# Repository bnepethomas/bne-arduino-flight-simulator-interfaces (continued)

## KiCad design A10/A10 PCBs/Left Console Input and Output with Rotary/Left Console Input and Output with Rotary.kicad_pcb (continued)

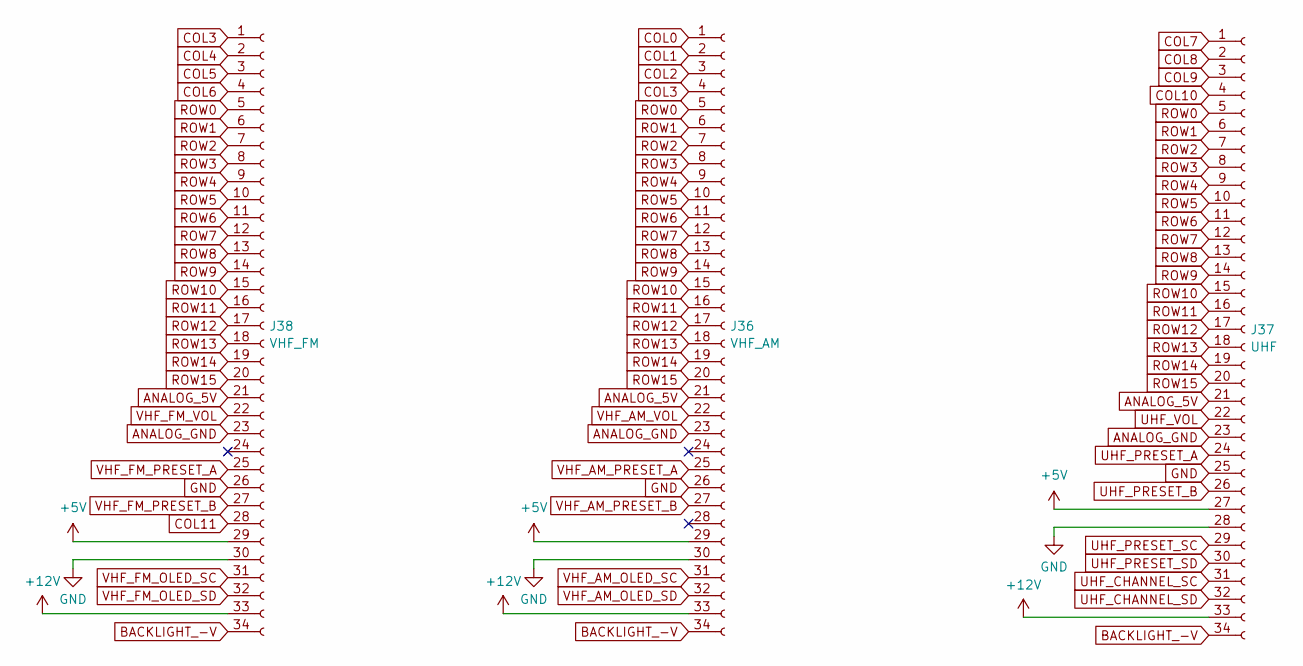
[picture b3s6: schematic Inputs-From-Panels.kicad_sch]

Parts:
J36: VHF_AM; IDC-Header_2x17_P2.54mm_Vertical
J37: UHF; IDC-Header_2x17_P2.54mm_Vertical
J38: VHF_FM; IDC-Header_2x17_P2.54mm_Vertical

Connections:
+12V: J36.33, J37.33, J38.33; also elsewhere on the board
BACKLIGHT_-V: J36.34, J37.34, J38.34; also elsewhere on the board
COL0: J36.1; also elsewhere on the board
COL1: J36.2; also elsewhere on the board
COL2: J36.3; also elsewhere on the board
COL3: J36.4, J38.1; also elsewhere on the board
COL4: J38.2; also elsewhere on the board
COL5: J38.3; also elsewhere on the board
COL6: J38.4; also elsewhere on the board
COL7: J37.1; also elsewhere on the board
COL8: J37.2; also elsewhere on the board
COL9: J37.3; also elsewhere on the board
COL10: J37.4; also elsewhere on the board
COL11: J38.28; also elsewhere on the board
ROW0: J36.5, J37.5, J38.5; also elsewhere on the board
ROW1: J36.6, J37.6, J38.6; also elsewhere on the board
ROW2: J36.7, J37.7, J38.7; also elsewhere on the board
ROW3: J36.8, J37.8, J38.8; also elsewhere on the board
ROW4: J36.9, J37.9, J38.9; also elsewhere on the board
ROW5: J36.10, J37.10, J38.10; also elsewhere on the board
ROW6: J36.11, J37.11, J38.11; also elsewhere on the board
ROW7: J36.12, J37.12, J38.12; also elsewhere on the board
ROW8: J36.13, J37.13, J38.13; also elsewhere on the board
ROW9: J36.14, J37.14, J38.14; also elsewhere on the board
ROW10: J36.15, J37.15, J38.15; also elsewhere on the board
ROW11: J36.16, J37.16, J38.16; also elsewhere on the board
ROW12: J36.17, J37.17, J38.17; also elsewhere on the board
ROW13: J36.18, J37.18, J38.18; also elsewhere on the board
ROW14: J36.19, J37.19, J38.19; also elsewhere on the board
ROW15: J36.20, J37.20, J38.20; also elsewhere on the board
UHF_CHANNEL_SC: J37.31; also elsewhere on the board
UHF_CHANNEL_SD: J37.32; also elsewhere on the board
UHF_PRESET_A: J37.24; also elsewhere on the board
UHF_PRESET_B: J37.26; also elsewhere on the board
UHF_PRESET_SC: J37.29; also elsewhere on the board
UHF_PRESET_SD: J37.30; also elsewhere on the board
UHF_VOL: J37.22; also elsewhere on the board
VHF_AM_OLED_SC: J36.31; also elsewhere on the board
VHF_AM_OLED_SD: J36.32; also elsewhere on the board
VHF_AM_PRESET_A: J36.25; also elsewhere on the board
VHF_AM_PRESET_B: J36.27; also elsewhere on the board
VHF_AM_VOL: J36.22; also elsewhere on the board
VHF_FM_OLED_SC: J38.31; also elsewhere on the board
VHF_FM_OLED_SD: J38.32; also elsewhere on the board
VHF_FM_PRESET_A: J38.25; also elsewhere on the board
VHF_FM_PRESET_B: J38.27; also elsewhere on the board
VHF_FM_VOL: J38.22; also elsewhere on the board

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
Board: 2 copper layers, 87 parts (0 on the bottom side), 144 nets, no tracks yet.

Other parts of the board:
MH1: MountingHole_3.2mm

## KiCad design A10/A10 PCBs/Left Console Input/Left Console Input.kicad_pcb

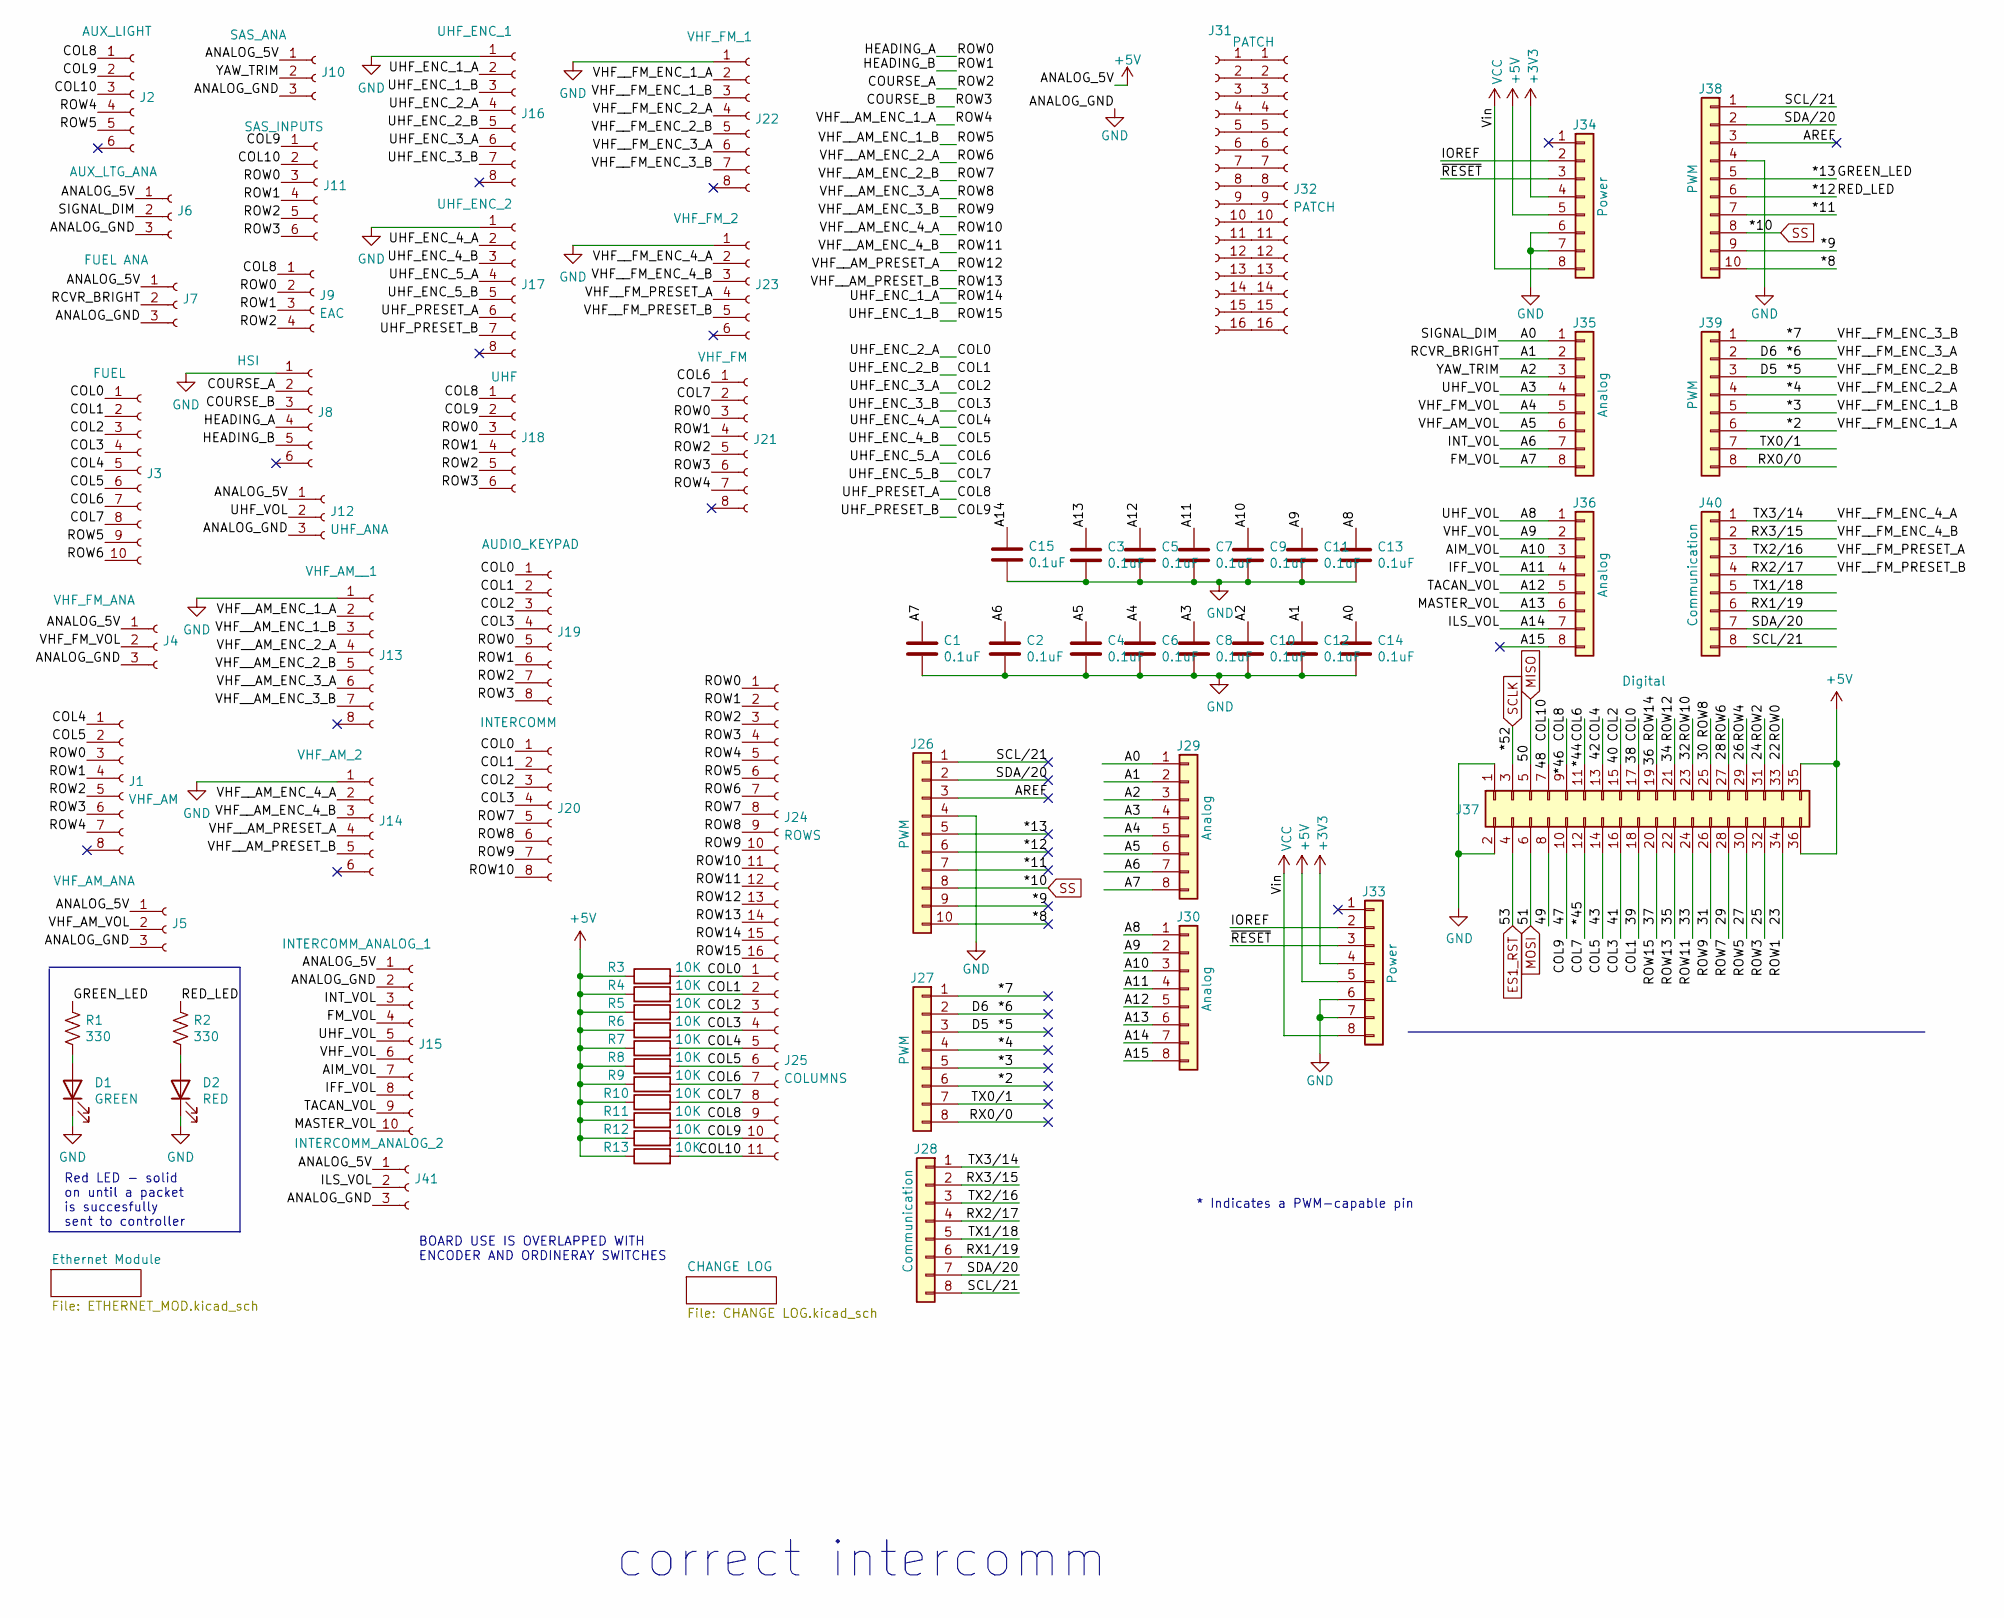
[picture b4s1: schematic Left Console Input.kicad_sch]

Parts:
C1, C2, C3, C4, C5, C6, C7, C8, C9, C10, C11, C12, C13, C14, C15: 0.1uF; C_Disc_D6.0mm_W2.5mm_P5.00mm
D1: GREEN; LED_D3.0mm
D2: RED; LED_D3.0mm
J1: VHF_AM; Molex_KK-254_AE-6410-08A_1x08_P2.54mm_Vertical
J2: AUX_LIGHT; Molex_KK-254_AE-6410-06A_1x06_P2.54mm_Vertical
J3: FUEL; Molex_KK-254_AE-6410-10A_1x10_P2.54mm_Vertical
J4: VHF_FM_ANA; Molex_KK-254_AE-6410-03A_1x03_P2.54mm_Vertical
J5: VHF_AM_ANA; Molex_KK-254_AE-6410-03A_1x03_P2.54mm_Vertical
J6: AUX_LTG_ANA; Molex_KK-254_AE-6410-03A_1x03_P2.54mm_Vertical
J7: FUEL ANA; Molex_KK-254_AE-6410-03A_1x03_P2.54mm_Vertical
J8: HSI; Molex_KK-254_AE-6410-06A_1x06_P2.54mm_Vertical
J9: EAC; Molex_KK-254_AE-6410-04A_1x04_P2.54mm_Vertical
J10: SAS_ANA; Molex_KK-254_AE-6410-03A_1x03_P2.54mm_Vertical
J11: SAS_INPUTS; Molex_KK-254_AE-6410-06A_1x06_P2.54mm_Vertical
J12: UHF_ANA; Molex_KK-254_AE-6410-03A_1x03_P2.54mm_Vertical
J13: VHF_AM__1; Molex_KK-254_AE-6410-08A_1x08_P2.54mm_Vertical
J14: VHF_AM_2; Molex_KK-254_AE-6410-06A_1x06_P2.54mm_Vertical
J15: INTERCOMM_ANALOG_1; Molex_KK-254_AE-6410-10A_1x10_P2.54mm_Vertical
J16: UHF_ENC_1; Molex_KK-254_AE-6410-08A_1x08_P2.54mm_Vertical
J17: UHF_ENC_2; Molex_KK-254_AE-6410-08A_1x08_P2.54mm_Vertical
J18: UHF; Molex_KK-254_AE-6410-06A_1x06_P2.54mm_Vertical
J19: AUDIO_KEYPAD; Molex_KK-254_AE-6410-08A_1x08_P2.54mm_Vertical
J20: INTERCOMM; Molex_KK-254_AE-6410-08A_1x08_P2.54mm_Vertical
J21: VHF_FM; Molex_KK-254_AE-6410-08A_1x08_P2.54mm_Vertical
J22: VHF_FM_1; Molex_KK-254_AE-6410-08A_1x08_P2.54mm_Vertical
J23: VHF_FM_2; Molex_KK-254_AE-6410-06A_1x06_P2.54mm_Vertical
J24: ROWS; PinHeader_1x16_P2.54mm_Vertical
J25: COLUMNS; PinHeader_1x11_P2.54mm_Vertical
J26, J38: PWM; PinSocket_1x10_P2.54mm_Vertical
J27, J39: PWM; PinSocket_1x08_P2.54mm_Vertical
J28, J40: Communication; PinSocket_1x08_P2.54mm_Vertical
J29, J30, J35, J36: Analog; PinSocket_1x08_P2.54mm_Vertical
J31, J32: PATCH; PinHeader_1x16_P2.54mm_Vertical
J33, J34: Power; PinSocket_1x08_P2.54mm_Vertical
J37: Digital; PinSocket_2x18_P2.54mm_Vertical
J41: INTERCOMM_ANALOG_2; Molex_KK-254_AE-6410-03A_1x03_P2.54mm_Vertical
R1, R2: 330; R_Axial_DIN0204_L3.6mm_D1.6mm_P2.54mm_Vertical
R3, R4, R5, R6, R7, R8, R9, R10, R11, R12, R13: 10K; R_Axial_DIN0204_L3.6mm_D1.6mm_P2.54mm_Vertical

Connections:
+3V3: J33.4, J34.4; also elsewhere on the board
+5V: J4.1, J5.1, J6.1, J7.1, J10.1, J12.1, J15.1, J33.5, J34.5, J37.35, J37.36, J41.1, R3.1, R4.1, R5.1, R6.1, R7.1, R8.1, R9.1, R10.1, R11.1, R12.1, R13.1
/22: J1.3, J8.4, J9.2, J11.3, J18.3, J19.5, J21.3, J24.1, J37.33
/23: J1.4, J8.5, J9.3, J11.4, J18.4, J19.6, J21.4, J24.2, J37.34
/24: J1.5, J8.2, J9.4, J11.5, J18.5, J19.7, J21.5, J24.3, J37.31
/25: J1.6, J8.3, J11.6, J18.6, J19.8, J21.6, J24.4, J37.32
/26: J1.7, J2.4, J13.2, J21.7, J24.5, J37.29
/27: J2.5, J3.9, J13.3, J24.6, J37.30
/28: J3.10, J13.4, J24.7, J37.27
/29: J13.5, J20.5, J24.8, J37.28
/30: J13.6, J20.6, J24.9, J37.25
/31: J13.7, J20.7, J24.10, J37.26
/32: J14.2, J20.8, J24.11, J37.23
/33: J14.3, J24.12, J37.24
/34: J14.4, J24.13, J37.21
/35: J14.5, J24.14, J37.22
/36: J16.2, J24.15, J37.19
/37: J16.3, J24.16, J37.20
/38: J3.1, J16.4, J19.1, J20.1, J25.1, J37.17, R3.2
/39: J3.2, J16.5, J19.2, J20.2, J25.2, J37.18, R4.2
/40: J3.3, J16.6, J19.3, J20.3, J25.3, J37.15, R5.2
/41: J3.4, J16.7, J19.4, J20.4, J25.4, J37.16, R6.2
/42: J1.1, J3.5, J17.2, J25.5, J37.13, R7.2
/43: J1.2, J3.6, J17.3, J25.6, J37.14, R8.2
/47: J2.2, J11.1, J17.7, J18.2, J25.10, J37.10, R12.2
/48: J2.3, J11.2, J25.11, J37.7, R13.2
/49: J37.8
/*2: J22.2, J27.6, J39.6
/*3: J22.3, J27.5, J39.5
/*4: J22.4, J27.4, J39.4
/*5: J22.5, J27.3, J39.3
/*6: J22.6, J27.2, J39.2
/*7: J22.7, J27.1, J39.1
/*8: J26.10, J38.10
/*9: J26.9, J38.9
/*11: J26.7, J38.7
/*12: J26.6, J38.6, R2.1
/*13: J26.5, J38.5, R1.1
/*44: J3.7, J17.4, J21.1, J25.7, J37.11, R9.2
/*45: J3.8, J17.5, J21.2, J25.8, J37.12, R10.2
/*46: J2.1, J9.1, J17.6, J18.1, J25.9, J37.9, R11.2
/A0: C14.1, J6.2, J29.1, J35.1
/A1: C12.1, J7.2, J29.2, J35.2
/A2: C10.1, J10.2, J29.3, J35.3
/A3: C8.1, C13.1, J12.2, J15.5, J29.4, J30.1, J35.4, J36.1
/A4: C6.1, J4.2, J29.5, J35.5
/A5: C4.1, J5.2, J29.6, J35.6
/A6: C2.1, J15.3, J29.7, J35.7
/A7: C1.1, J15.4, J29.8, J35.8
/A9: C11.1, J15.6, J30.2, J36.2
/A10: C9.1, J15.7, J30.3, J36.3
/A11: C7.1, J15.8, J30.4, J36.4
/A12: C5.1, J15.9, J30.5, J36.5
/A13: C3.1, J15.10, J30.6, J36.6
/A14: C15.1, J30.7, J36.7, J41.2
/A15: J30.8, J36.8
/AREF: J26.3, J38.3
/IOREF: J33.2, J34.2
/RX0/0: J27.8, J39.8
/RX1/19: J28.6, J40.6
/RX2/17: J23.5, J28.4, J40.4
/RX3/15: J23.3, J28.2, J40.2
/SCL/21: J26.1, J28.8, J38.1, J40.8
/SDA/20: J26.2, J28.7, J38.2, J40.7
/TX0/1: J27.7, J39.7
/TX1/18: J28.5, J40.5
/TX2/16: J23.4, J28.3, J40.3
/TX3/14: J23.2, J28.1, J40.1
/~RESET: J33.3, J34.3
ES1_RST: J37.4; also elsewhere on the board
GND: C1.2, C2.2, C3.2, C4.2, C5.2, C6.2, C7.2, C8.2, C9.2, C10.2, C11.2, C12.2, C13.2, C14.2, C15.2, D1.1 (K), D2.1 (K), J4.3, J5.3, J6.3, J7.3, J8.1, J10.3, J12.3, J13.1, J14.1, J15.2, J16.1, J17.1, J22.1, J23.1, J26.4, J33.6, J33.7, J34.6, J34.7, J37.1, J37.2, J38.4, J41.3; also elsewhere on the board
MISO: J37.5; also elsewhere on the board
MOSI: J37.6; also elsewhere on the board
unnamed: D1.2 (A), R1.2
unnamed: D2.2 (A), R2.2
unnamed: J31.1, J32.1
unnamed: J31.2, J32.2
unnamed: J31.3, J32.3
unnamed: J31.4, J32.4
unnamed: J31.5, J32.5
unnamed: J31.6, J32.6
unnamed: J31.7, J32.7
unnamed: J31.8, J32.8
unnamed: J31.9, J32.9
unnamed: J31.10, J32.10
unnamed: J31.11, J32.11
unnamed: J31.12, J32.12
unnamed: J31.13, J32.13
unnamed: J31.14, J32.14
unnamed: J31.15, J32.15
unnamed: J31.16, J32.16
SCLK: J37.3; also elsewhere on the board
SS: J26.8, J38.8; also elsewhere on the board
VCC: J33.8, J34.8

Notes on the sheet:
BOARD USE IS OVERLAPPED WITH ENCODER AND ORDINERAY SWITCHES
Red LED - solid on until a packet is succesfully sent to controller
* Indicates a PWM-capable pin
correct intercomm

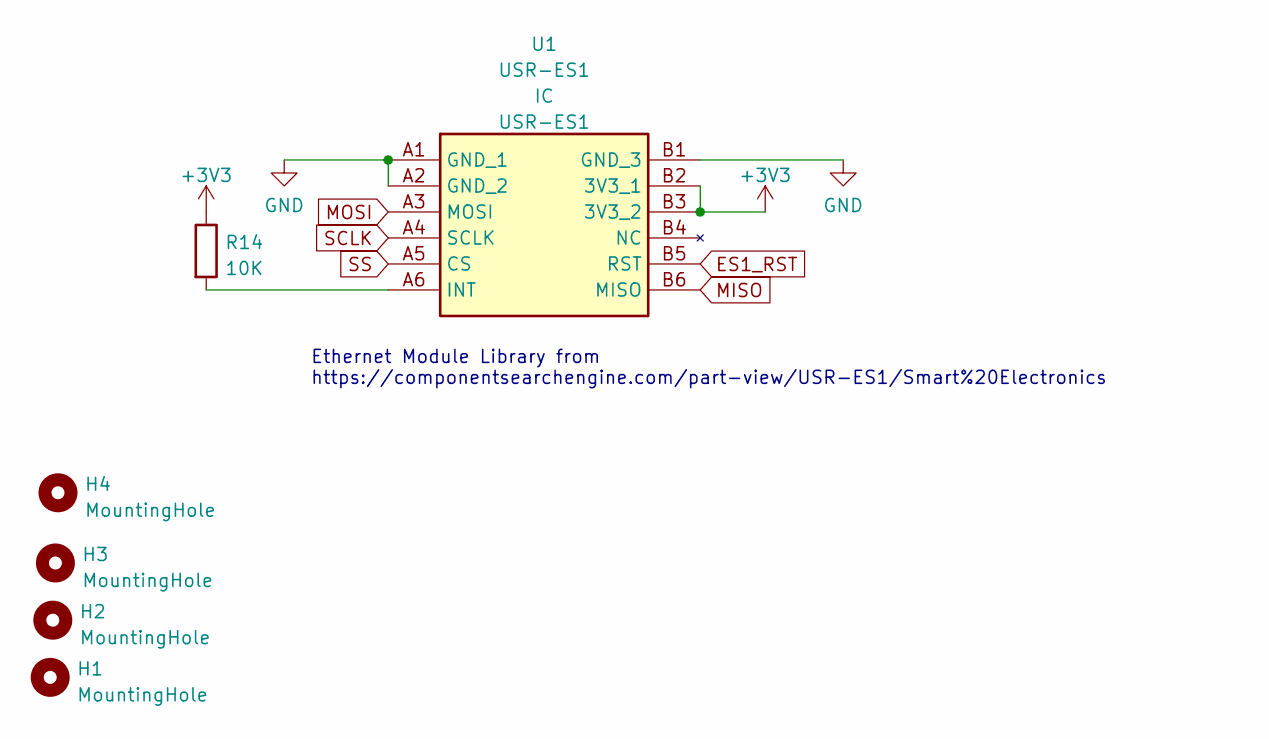
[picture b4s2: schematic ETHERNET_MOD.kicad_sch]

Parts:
H1, H2, H3, H4: MountingHole; MountingHole_3.2mm
R14: 10K; R_Axial_DIN0204_L3.6mm_D1.6mm_P2.54mm_Vertical
U1: USR-ES1; USRES1; Manufacturer_Part_Number USR-ES1

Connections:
+3V3: R14.1, U1.B2 (3V3_1), U1.B3 (3V3_2); also elsewhere on the board
ES1_RST: U1.B5 (RST); also elsewhere on the board
GND: U1.A1 (GND_1), U1.A2 (GND_2), U1.B1 (GND_3); also elsewhere on the board
MISO: U1.B6 (MISO); also elsewhere on the board
MOSI: U1.A3 (MOSI); also elsewhere on the board
unnamed: R14.2, U1.A6 (INT)
SCLK: U1.A4 (SCLK); also elsewhere on the board
SS: U1.A5 (CS); also elsewhere on the board

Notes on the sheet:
Ethernet Module Library from https://componentsearchengine.com/part-view/USR-ES1/Smart%20Electronics

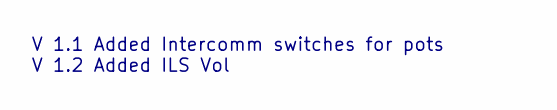
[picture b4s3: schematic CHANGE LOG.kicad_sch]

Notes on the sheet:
V 1.1 Added Intercomm switches for pots V 1.2 Added ILS Vol

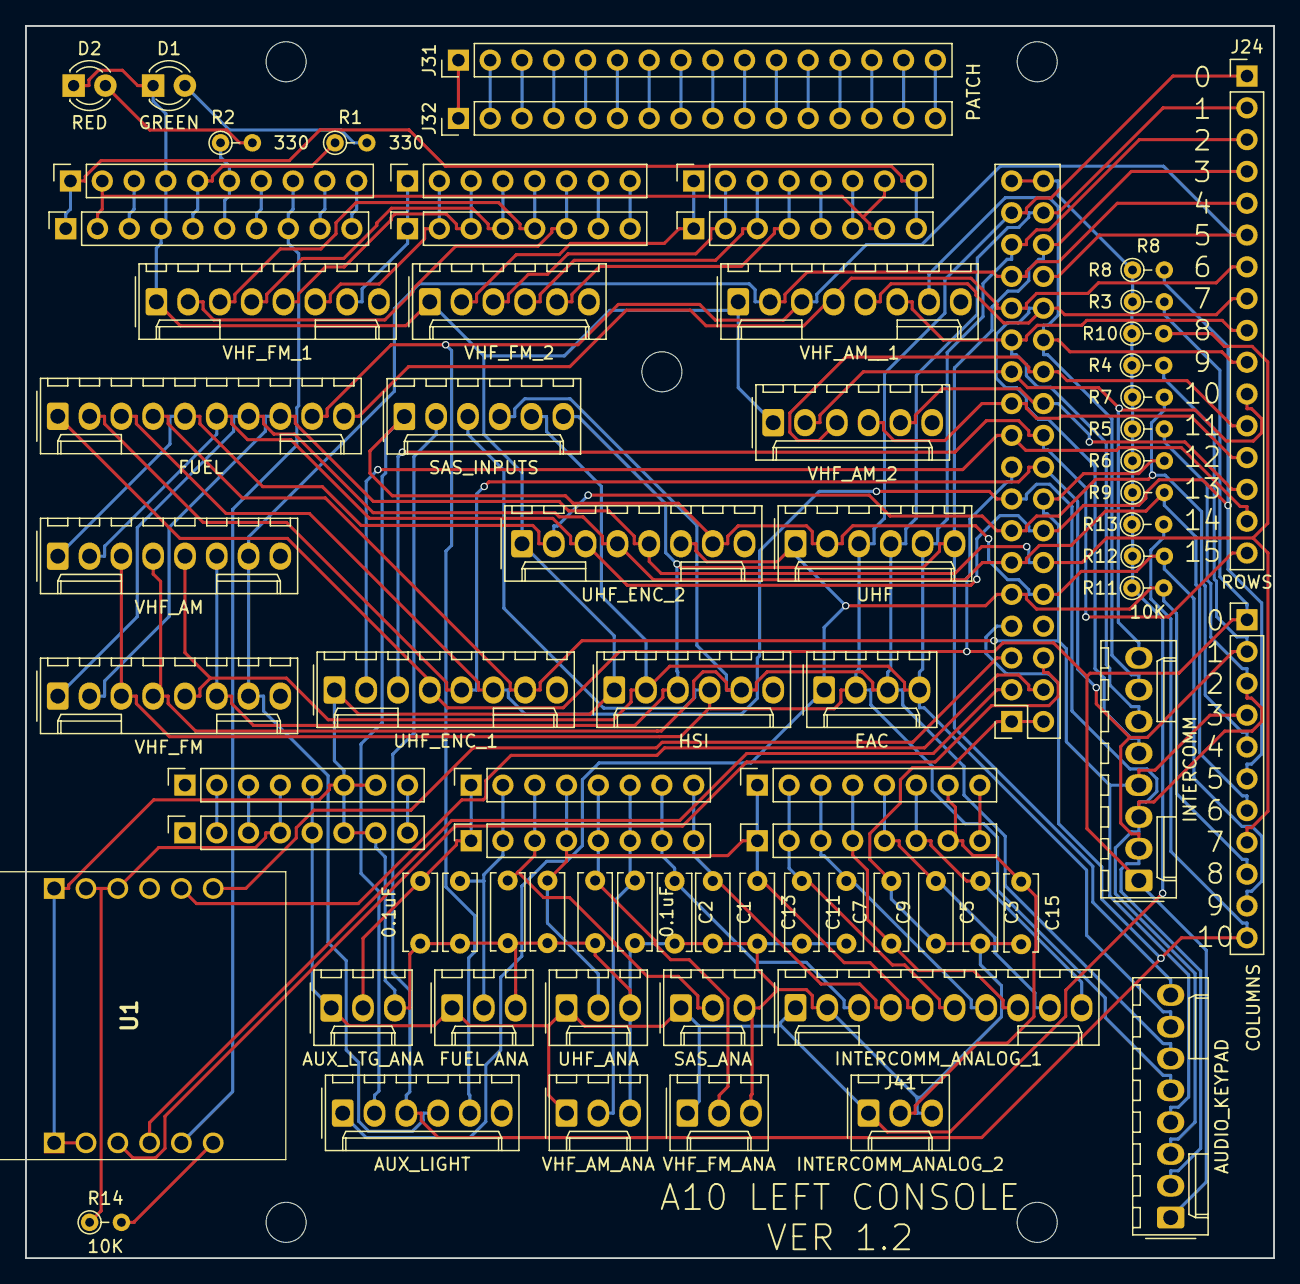
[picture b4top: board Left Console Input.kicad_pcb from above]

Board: 2 copper layers, 99.7 x 98.4 mm, 78 parts (0 on the bottom side), 94 nets.

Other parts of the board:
MH1: MountingHole_3.2mm

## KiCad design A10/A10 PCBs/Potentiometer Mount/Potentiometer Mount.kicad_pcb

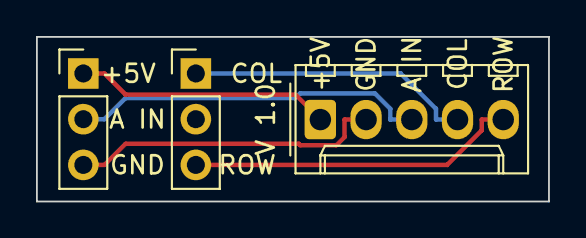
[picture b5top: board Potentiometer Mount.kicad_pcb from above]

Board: 2 copper layers, 28.4 x 9.1 mm, 3 parts (0 on the bottom side), 5 nets.

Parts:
J1: POT; Molex_KK-254_AE-6410-05A_1x05_P2.54mm_Vertical
RV1: R_Potentiometer_US; PinHeader_1x03_P2.54mm_Vertical
SW1: SW_SPDT; PinHeader_1x03_P2.54mm_Vertical

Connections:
/+5V: J1.1, RV1.1
/ANALOG_GND: J1.2, RV1.3
/ANALOG_IN: J1.3, RV1.2
/SWITCH_COL: J1.4, SW1.1 (A)
/SWITCH_ROW: J1.5, SW1.3 (C)

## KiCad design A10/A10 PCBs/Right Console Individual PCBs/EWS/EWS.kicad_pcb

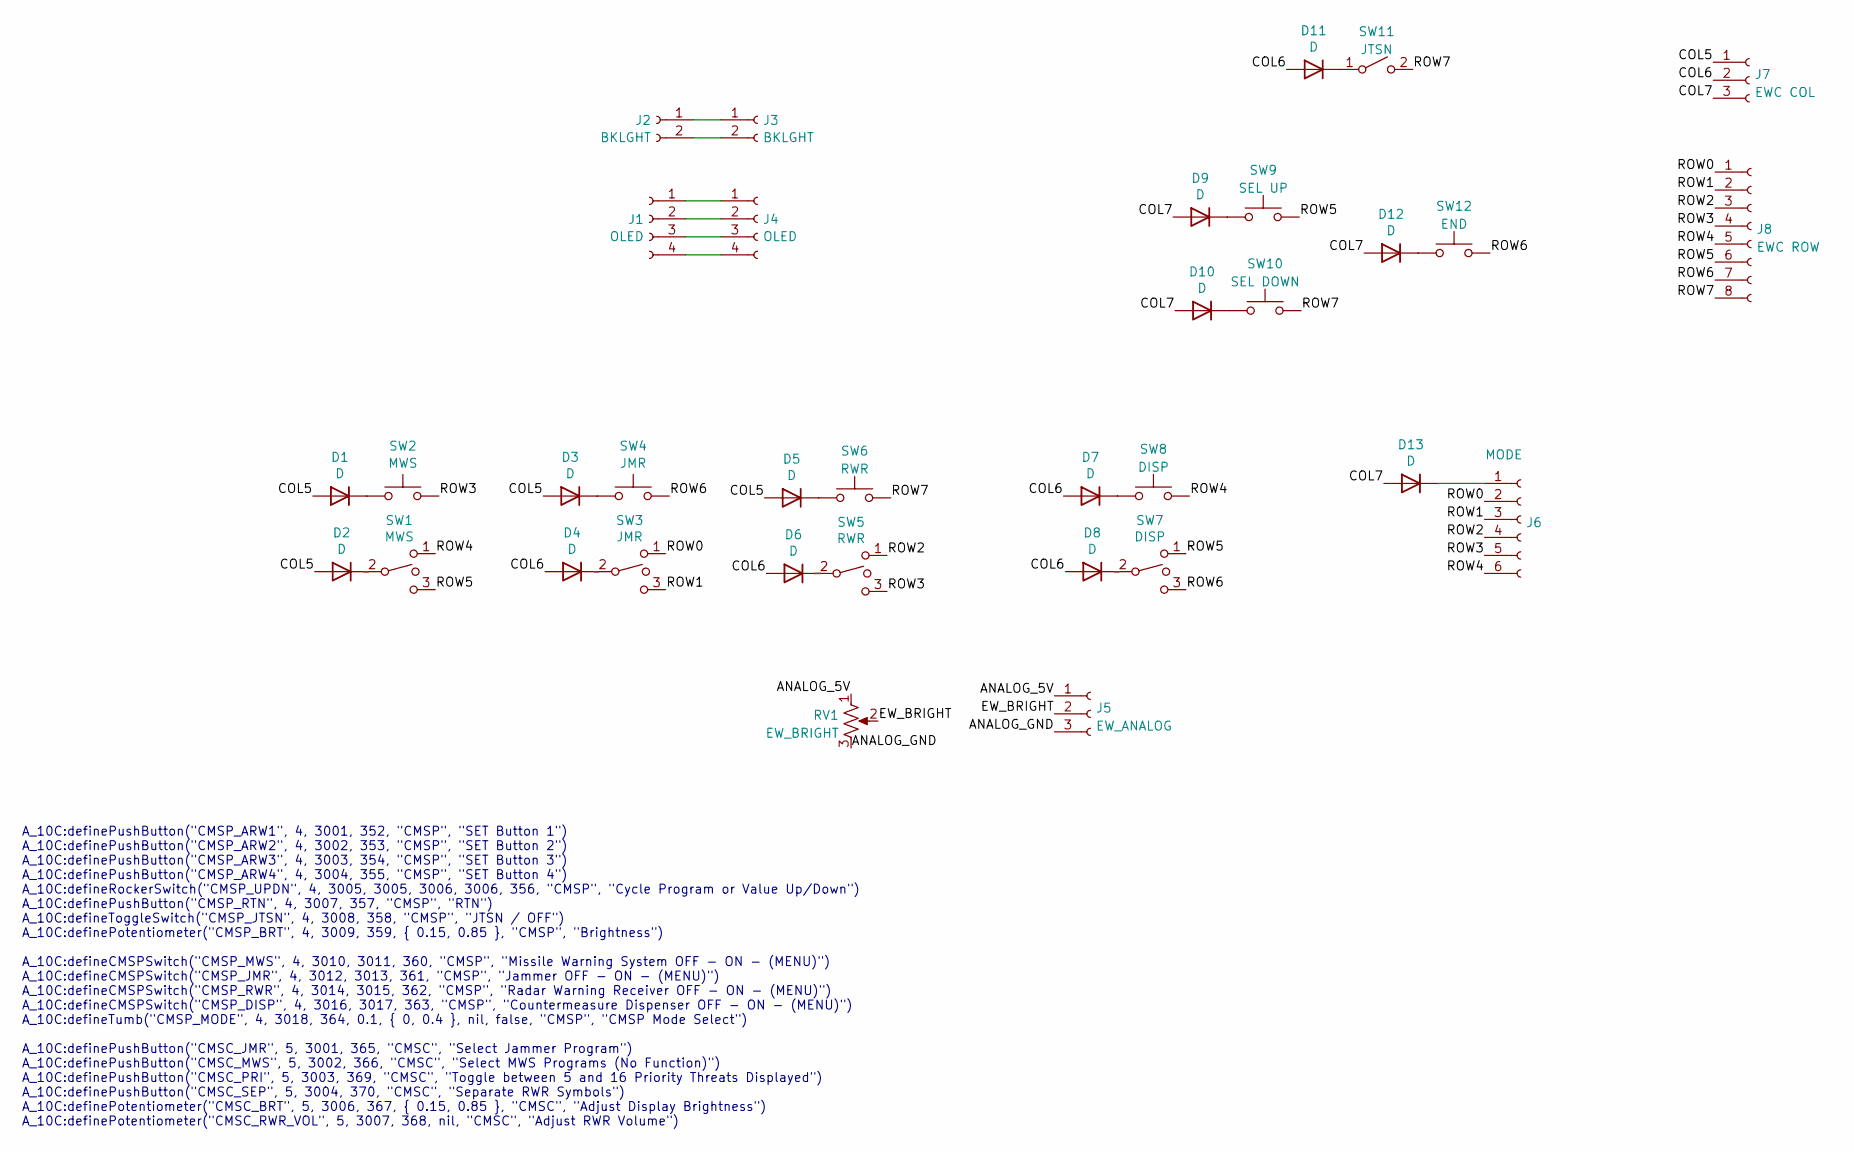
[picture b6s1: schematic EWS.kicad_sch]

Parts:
D1, D2, D3, D4, D5, D6, D7, D8, D9, D10, D11, D12, D13: D; D_A-405_P2.54mm_Vertical_AnodeUp
J1, J4: OLED; Molex_KK-254_AE-6410-04A_1x04_P2.54mm_Vertical
J2, J3: BKLGHT; Molex_KK-254_AE-6410-02A_1x02_P2.54mm_Vertical
J5: EW_ANALOG; Molex_KK-254_AE-6410-03A_1x03_P2.54mm_Vertical
J6: MODE; Molex_KK-254_AE-6410-06A_1x06_P2.54mm_Vertical
J7: EWC COL; Molex_KK-254_AE-6410-03A_1x03_P2.54mm_Vertical
J8: EWC ROW; Molex_KK-254_AE-6410-08A_1x08_P2.54mm_Vertical
RV1: EW_BRIGHT; Molex_KK-254_AE-6410-03A_1x03_P2.54mm_Vertical
SW1: MWS; Molex_KK-254_AE-6410-03A_1x03_P2.54mm_Vertical
SW2: MWS; Molex_KK-254_AE-6410-02A_1x02_P2.54mm_Vertical
SW3: JMR; Molex_KK-254_AE-6410-03A_1x03_P2.54mm_Vertical
SW4: JMR; Molex_KK-254_AE-6410-02A_1x02_P2.54mm_Vertical
SW5: RWR; Molex_KK-254_AE-6410-03A_1x03_P2.54mm_Vertical
SW6: RWR; Molex_KK-254_AE-6410-02A_1x02_P2.54mm_Vertical
SW7: DISP; Molex_KK-254_AE-6410-03A_1x03_P2.54mm_Vertical
SW8: DISP; Molex_KK-254_AE-6410-02A_1x02_P2.54mm_Vertical
SW9: SEL UP; Molex_KK-254_AE-6410-02A_1x02_P2.54mm_Vertical
SW10: SEL DOWN; Molex_KK-254_AE-6410-02A_1x02_P2.54mm_Vertical
SW11: JTSN; Molex_KK-254_AE-6410-02A_1x02_P2.54mm_Vertical
SW12: END; Molex_KK-254_AE-6410-02A_1x02_P2.54mm_Vertical

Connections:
/ANALOG_5V: J5.1, RV1.1
/ANALOG_GND: J5.3, RV1.3
/COL5: D1.2 (A), D2.2 (A), D3.2 (A), D5.2 (A), J7.1
/COL6: D4.2 (A), D6.2 (A), D7.2 (A), D8.2 (A), D11.2 (A), J7.2
/COL7: D9.2 (A), D10.2 (A), D12.2 (A), D13.2 (A), J7.3
/EW_BRIGHT: J5.2, RV1.2
/ROW0: J6.2, J8.1, SW3.1
/ROW1: J6.3, J8.2, SW3.3
/ROW2: J6.4, J8.3, SW5.1
/ROW3: J6.5, J8.4, SW2.2, SW5.3
/ROW4: J6.6, J8.5, SW1.1, SW8.2
/ROW5: J8.6, SW1.3, SW7.1, SW9.2
/ROW6: J8.7, SW4.2, SW7.3, SW12.2
/ROW7: J8.8, SW6.2, SW10.2, SW11.2 (B)
unnamed: D1.1 (K), SW2.1
unnamed: D2.1 (K), SW1.2
unnamed: D3.1 (K), SW4.1
unnamed: D4.1 (K), SW3.2
unnamed: D5.1 (K), SW6.1
unnamed: D6.1 (K), SW5.2
unnamed: D7.1 (K), SW8.1
unnamed: D8.1 (K), SW7.2
unnamed: D9.1 (K), SW9.1
unnamed: D10.1 (K), SW10.1
unnamed: D11.1 (K), SW11.1 (A)
unnamed: D12.1 (K), SW12.1
unnamed: D13.1 (K), J6.1
unnamed: J1.1, J4.1
unnamed: J1.2, J4.2
unnamed: J1.3, J4.3
unnamed: J1.4, J4.4
unnamed: J2.1, J3.1
unnamed: J2.2, J3.2

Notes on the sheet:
A_10C:definePushButton("CMSP_ARW1", 4, 3001, 352, "CMSP", "SET Button 1") A_10C:definePushButton("CMSP_ARW2", 4, 3002, 353, "CMSP", "SET Button 2") A_10C:definePushButton("CMSP_ARW3", 4, 3003, 354, "CMSP", "SET Button 3") A_10C:definePushButton("CMSP_ARW4", 4, 3004, 355, "CMSP", "SET Button 4") A_1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

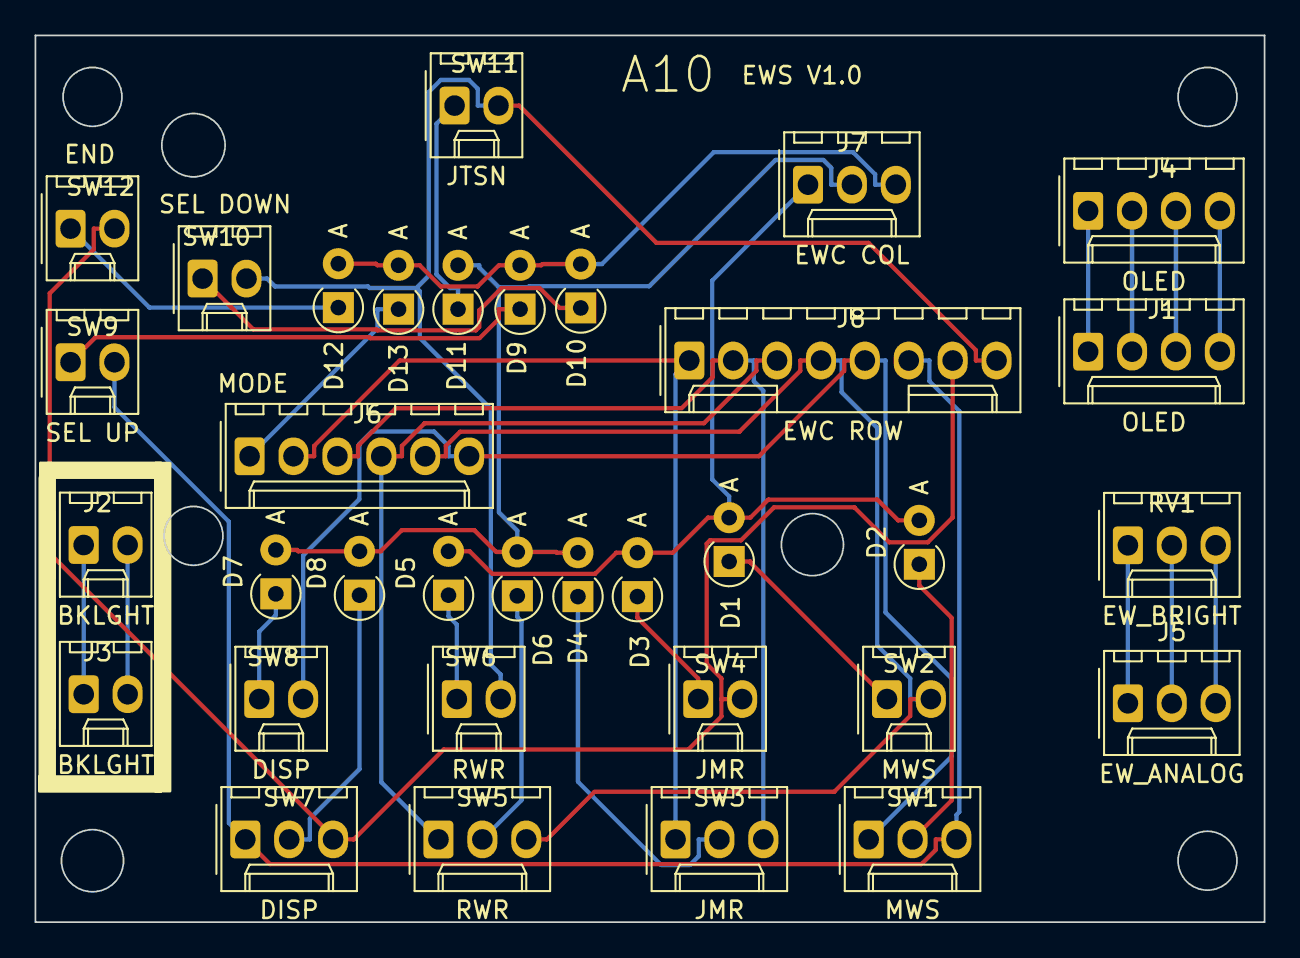
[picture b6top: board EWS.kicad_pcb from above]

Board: 2 copper layers, 71.1 x 51.3 mm, 34 parts (0 on the bottom side), 33 nets.

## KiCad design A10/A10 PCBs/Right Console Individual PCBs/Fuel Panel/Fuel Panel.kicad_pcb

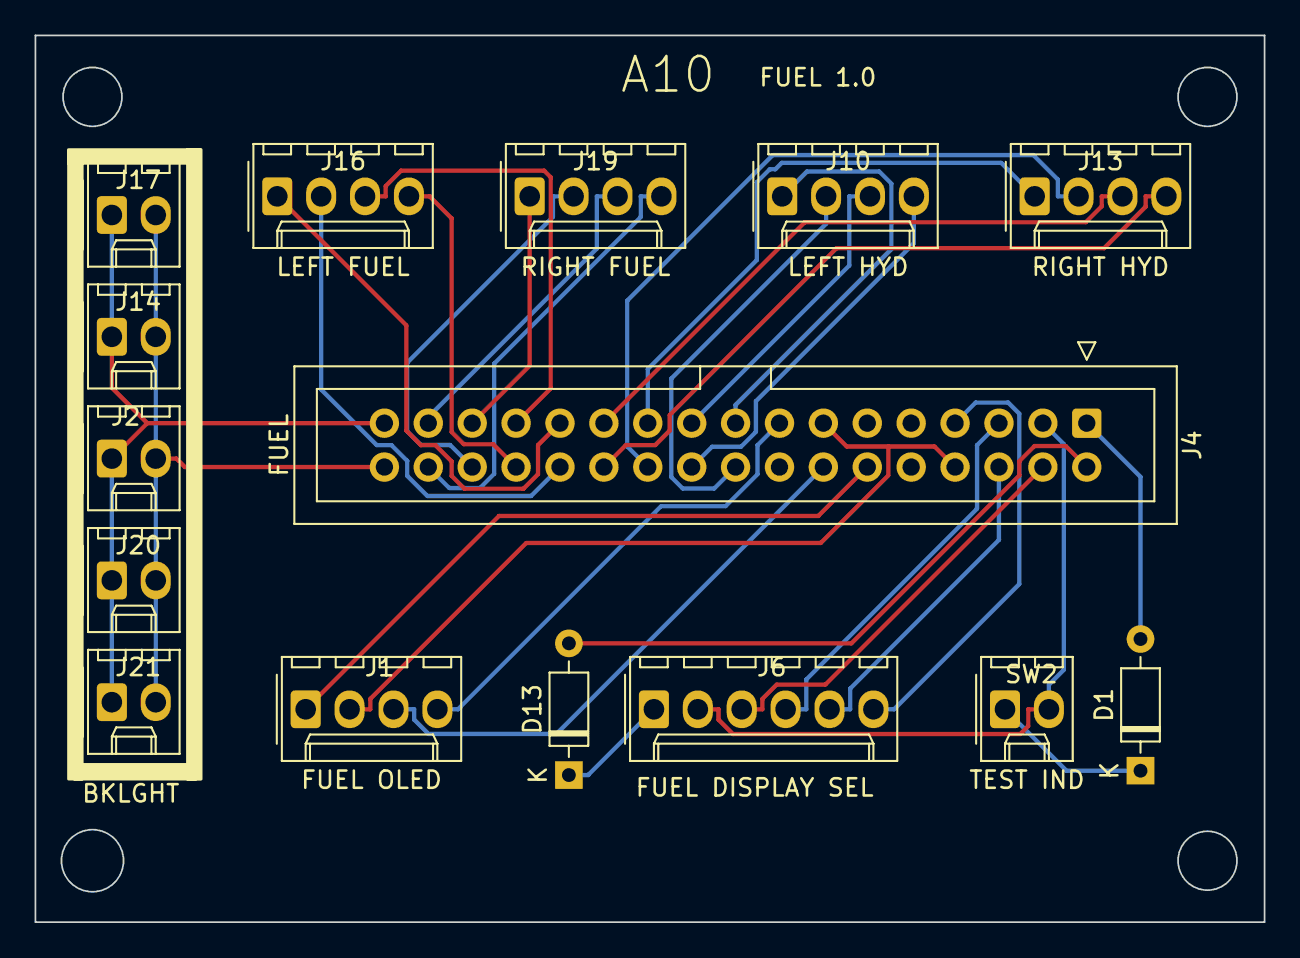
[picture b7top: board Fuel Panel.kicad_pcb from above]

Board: 2 copper layers, 71.1 x 51.3 mm, 15 parts (0 on the bottom side), 31 nets.

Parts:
D1, D13: D; D_DO-35_SOD27_P7.62mm_Horizontal
J1: FUEL OLED; Molex_KK-254_AE-6410-04A_1x04_P2.54mm_Vertical
J2, J14, J17, J20, J21: BKLGHT; Molex_KK-254_AE-6410-02A_1x02_P2.54mm_Vertical
J4: FUEL; IDC-Header_2x17_P2.54mm_Vertical
J6: FUEL DISPLAY SEL; Molex_KK-254_AE-6410-06A_1x06_P2.54mm_Vertical
J10: LEFT HYD; Molex_KK-254_AE-6410-04A_1x04_P2.54mm_Vertical
J13: RIGHT HYD; Molex_KK-254_AE-6410-04A_1x04_P2.54mm_Vertical
J16: LEFT FUEL; Molex_KK-254_AE-6410-04A_1x04_P2.54mm_Vertical
J19: RIGHT FUEL; Molex_KK-254_AE-6410-04A_1x04_P2.54mm_Vertical
SW2: TEST IND; Molex_KK-254_AE-6410-02A_1x02_P2.54mm_Vertical

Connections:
+5V: J1.1, J4.12
+12V: J2.1, J4.33, J14.1, J17.1, J20.1, J21.1
BACKLIGHT_-V: J2.2, J4.34, J14.2, J17.2, J20.2, J21.2
COL0: D1.2 (A), J4.1
COL1: D13.2 (A), J4.2
FUEL_OLED_SC: J1.3, J4.14
FUEL_OLED_SD: J1.4, J4.15
GND: J1.2, J4.8, J4.13
unnamed: D1.1 (K), SW2.1
unnamed: D13.1 (K), J6.1
ROW0: J4.3, J6.2, SW2.2
ROW1: J4.4, J6.3
ROW2: J4.5, J6.4
ROW3: J4.6, J6.5
ROW4: J4.7, J6.6
STEP_HYD_RIGHT_A: J4.21, J13.1
STEP_HYD_RIGHT_B: J4.22, J13.2
STEP_HYD_RIGHT_C: J4.23, J13.3
STEP_HYD_RIGHT_D: J4.24, J13.4
STEP_LEFT_FUEL_A: J4.25, J16.1
STEP_LEFT_FUEL_B: J4.26, J16.2
STEP_LEFT_FUEL_C: J4.27, J16.3
STEP_LEFT_FUEL_D: J4.28, J16.4
STEP_LEFT_HYD_A: J4.17, J10.1
STEP_LEFT_HYD_B: J4.18, J10.2
STEP_LEFT_HYD_C: J4.19, J10.3
STEP_LEFT_HYD_D: J4.20, J10.4
STEP_RIGHT_FUEL_A: J4.29, J19.1
STEP_RIGHT_FUEL_B: J4.30, J19.2
STEP_RIGHT_FUEL_C: J4.31, J19.3
STEP_RIGHT_FUEL_D: J4.32, J19.4
